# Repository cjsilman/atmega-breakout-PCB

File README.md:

# atmega-breakout-PCB
This PCB project is meant to replicate a simple atmega32u4 microcontroller board with GPIO pinouts. It contains a USB port for programming and powering.

As the idea of designing my own PCB always fascinated me, I thought it would be interesting to give designing one a shot!

While searching around the market for which MCU to use, I choose the ATMEGA32u4 as it comes with a pre-installed bootloader, allowing you to program it via the USB right from the start.
This MCU also came with USB support, something I wanted in my PCB. It was quite the learning process. I feel like I learned quite a bit that I want to share.

To begin with, you typically start by setting up the main components the MCU needs to function: it's power and crystal oscillator.

When designing the schematic for the VCC pins, it is best practice to place a 100nF decoupling capacitor for each pin along with a 10uF bulk decoupling capcitor to help with the stabilization of the input voltage.

For the crystal oscillator, you'll want to calculate the value of the decoupling capacitors associated with it. While it is standard practice to use 22pF capacitors, it is important to choose proper capacitor values to allow for more accurate and stable results from the crystal.

  - The capacitor values can be calculated from a formula like this:
    - C1, C2 = 2*Cload-2*Cstray

  - Cload, or the load capacitance, is retrieved from the datasheet of the specific crystal you choose.
  - Cstray, or the stray capacitance, is typically between a value of 3-5pF.
    - Cstray is the parasitic capacitance formed between two traces separated by a dielectric (in more layman terms, it is caused by a potential difference generated by current carrying traces running in close proximity to one another)

If you ever find yourself lost, the MCU datasheet typically has a lot of guidelines for when it comes to designing with that specific IC. Make sure to follow them.

I placed a GND plane on the entire bottom layer of my PCB. This allows for better signal integrity and more resistance to interference, it also allows you to create a via to ground wherever you need it.
     
  - Using one via per GND pin reduces the issue of potentially creating a ground loop and minimizes noise.

I discovered that USBs are typically designed with something known as "differential pairs"

  - On the schematic below, you can see D+ and D-, the postive and negative sign typically denote differential pairings
  - Differential pair PCB routing is used to create a balanced transmission system able to carry equal and opposite signals.
      - These two lines are usually of equal length
  - Having differential pairs also reduces any unwanted impedence

If you have any advice for me or would like to talk to me about certain design decisions feel free to give me a message! I am always looking to learn new things and improve my knowledge

# Full Schematic

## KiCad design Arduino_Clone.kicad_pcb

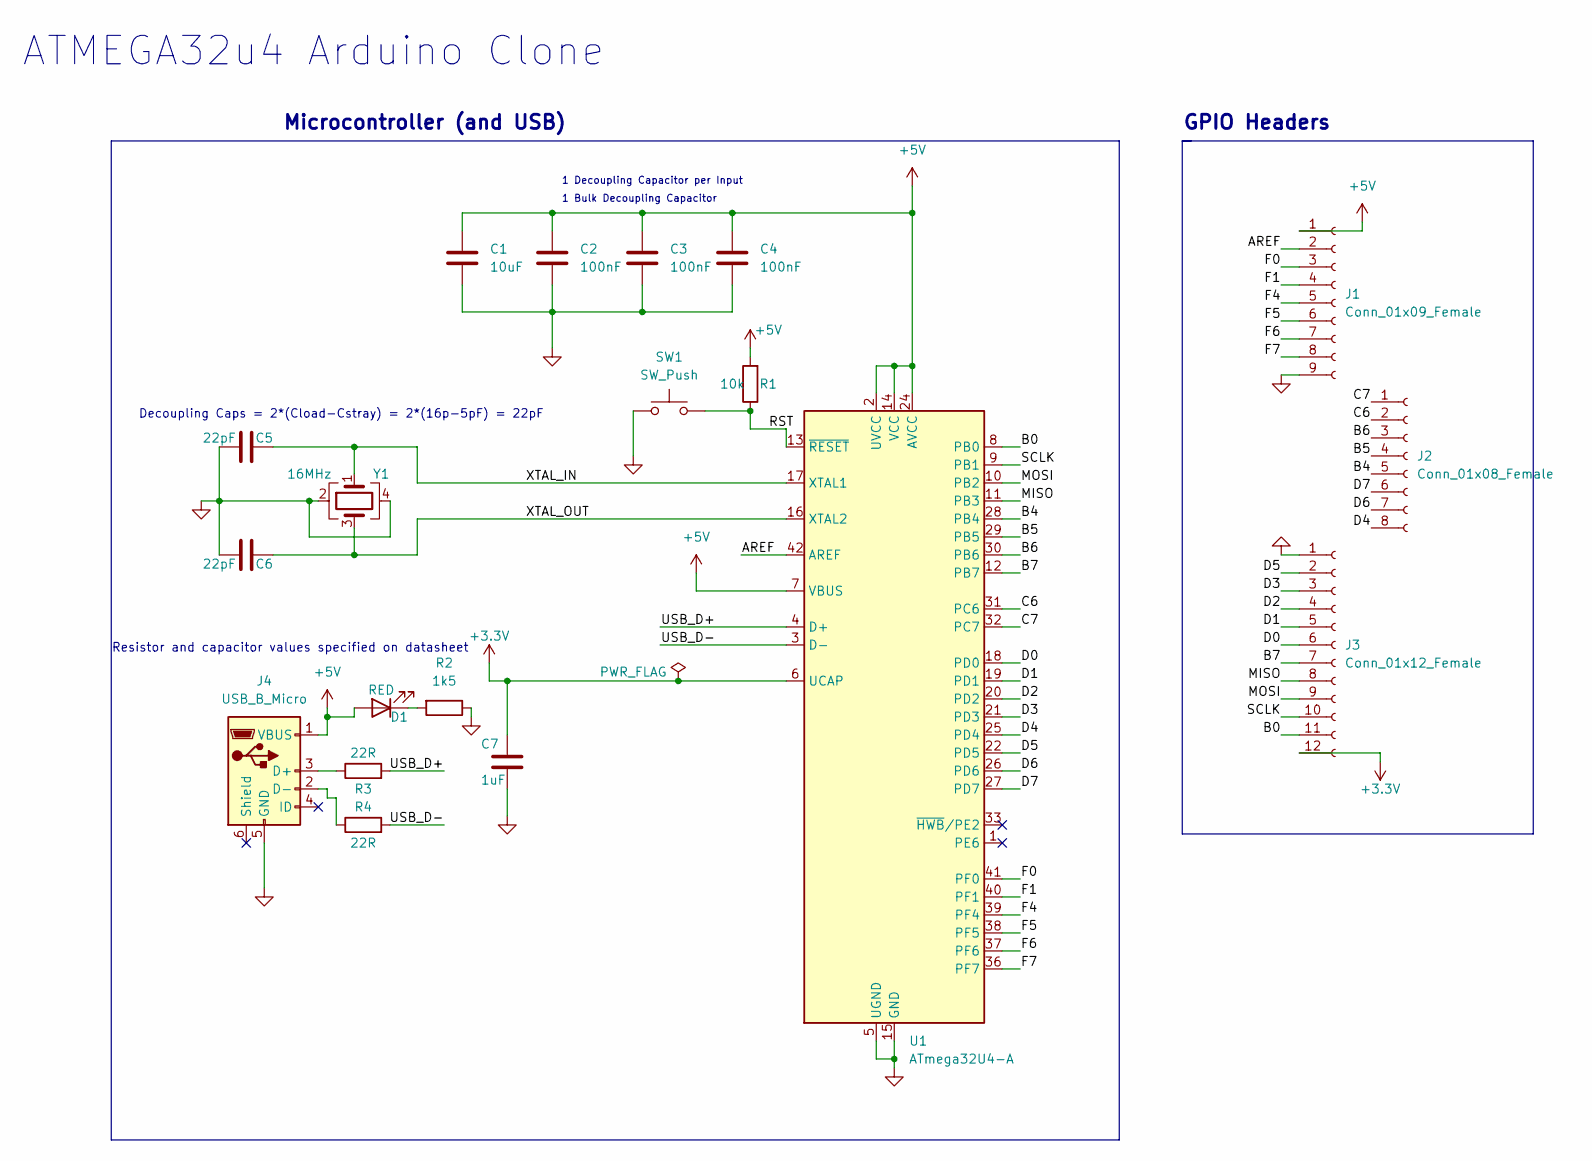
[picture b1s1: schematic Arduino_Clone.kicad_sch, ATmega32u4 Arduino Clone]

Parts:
C1: 10uF; C_0805_2012Metric_Pad1.18x1.45mm_HandSolder
C2, C3, C4: 100nF; C_0805_2012Metric_Pad1.18x1.45mm_HandSolder
C5, C6: 22pF; C_0805_2012Metric_Pad1.18x1.45mm_HandSolder
C7: 1uF; C_0805_2012Metric_Pad1.18x1.45mm_HandSolder
D1: RED; LED_0805_2012Metric_Pad1.15x1.40mm_HandSolder
J1: Conn_01x09_Female; PinSocket_1x09_P2.54mm_Vertical
J2: Conn_01x08_Female; PinSocket_1x08_P2.54mm_Vertical
J3: Conn_01x12_Female; PinSocket_1x12_P2.54mm_Vertical
J4: USB_B_Micro; USB_Micro-B_Wuerth_629105150521
R1: 10k; R_0805_2012Metric_Pad1.20x1.40mm_HandSolder
R2: 1k5; R_0805_2012Metric_Pad1.20x1.40mm_HandSolder
R3, R4: 22R; R_0805_2012Metric_Pad1.20x1.40mm_HandSolder
SW1: SW_Push; SW_Push_1P1T_NO_6x6mm_H9.5mm
U1: ATmega32U4-A; TQFP-44_10x10mm_P0.8mm
Y1: 16MHz; Crystal_SMD_3225-4Pin_3.2x2.5mm

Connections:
+3.3V: C7.1, J3.12, U1.6 (UCAP)
+5V: C1.1, C2.1, C3.1, C4.1, D1.2 (A), J1.1, J4.1 (VBUS), R1.2, U1.2 (UVCC), U1.7 (VBUS), U1.14 (VCC), U1.24 (AVCC), U1.34 (VCC), U1.44 (AVCC)
/AREF: J1.2, U1.42 (AREF)
/B0: J3.11, U1.8 (PB0)
/B4: J2.5, U1.28 (PB4)
/B5: J2.4, U1.29 (PB5)
/B6: J2.3, U1.30 (PB6)
/B7: J3.7, U1.12 (PB7)
/C6: J2.2, U1.31 (PC6)
/C7: J2.1, U1.32 (PC7)
/D0: J3.6, U1.18 (PD0)
/D1: J3.5, U1.19 (PD1)
/D2: J3.4, U1.20 (PD2)
/D3: J3.3, U1.21 (PD3)
/D4: J2.8, U1.25 (PD4)
/D5: J3.2, U1.22 (PD5)
/D6: J2.7, U1.26 (PD6)
/D7: J2.6, U1.27 (PD7)
/F0: J1.3, U1.41 (PF0)
/F1: J1.4, U1.40 (PF1)
/F4: J1.5, U1.39 (PF4)
/F5: J1.6, U1.38 (PF5)
/F6: J1.7, U1.37 (PF6)
/F7: J1.8, U1.36 (PF7)
/MISO: J3.8, U1.11 (PB3)
/MOSI: J3.9, U1.10 (PB2)
/RST: R1.1, SW1.2, U1.13 (~RESET)
/SCLK: J3.10, U1.9 (PB1)
/USB_D+: R3.2, U1.4 (D+)
/USB_D-: R4.2, U1.3 (D-)
/XTAL_IN: C5.2, U1.17 (XTAL1), Y1.1
/XTAL_OUT: C6.2, U1.16 (XTAL2), Y1.3
GND: C1.2, C2.2, C3.2, C4.2, C5.1, C6.1, C7.2, J1.9, J3.1, J4.5 (GND), R2.1, SW1.1, U1.5 (UGND), U1.15 (GND), U1.23 (GND), U1.35 (GND), U1.43 (GND), Y1.2, Y1.4
unnamed: D1.1 (K), R2.2
unnamed: J4.2 (D-), R4.1
unnamed: J4.3 (D+), R3.1

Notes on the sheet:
1 Bulk Decoupling Capacitor
Resistor and capacitor values specified on datasheet
GPIO Headers
ATMEGA32u4 Arduino Clone
1 Decoupling Capacitor per Input
Microcontroller (and USB)
Decoupling Caps = 2*(Cload-Cstray) = 2*(16p-5pF) = 22pF

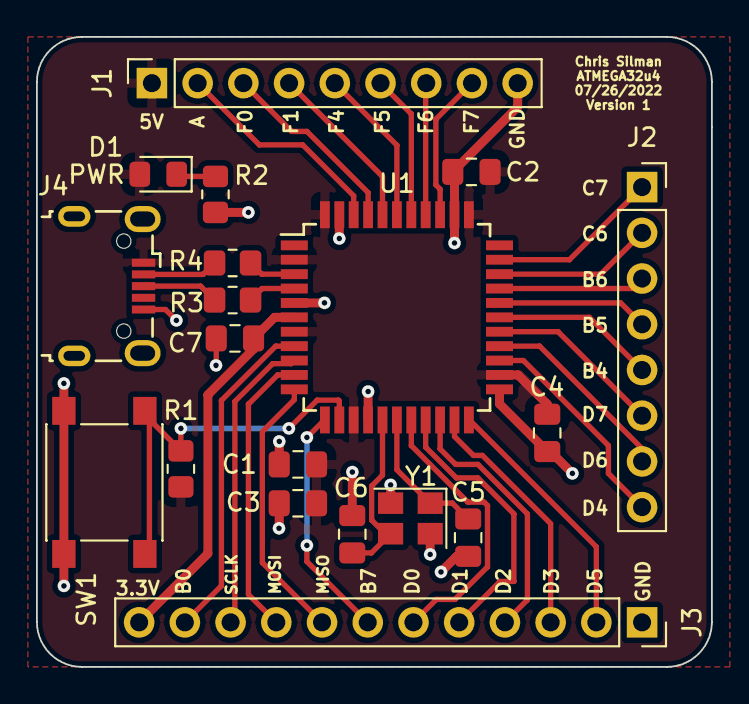
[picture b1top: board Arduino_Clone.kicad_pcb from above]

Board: 2 copper layers, 37.5 x 35.0 mm, 19 parts (0 on the bottom side), 36 nets.

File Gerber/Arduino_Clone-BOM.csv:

"Source:","G:\Desktop\KiCAD projects\Arduino_Clone\Arduino_Clone.kicad_sch"
"Date:","7/26/2022 7:15:45 PM"
"Tool:","Eeschema (6.0.6)"
"Generator:","G:\Program Files\KiCad\6.0\bin\scripting\plugins/bom_csv_grouped_by_value_with_fp.py"
"Component Count:","19"
"Ref","Qnty","Value","Cmp name","Footprint","Description","Vendor"
"C1, ","1","10uF","C","Capacitor_SMD:C_0805_2012Metric_Pad1.18x1.45mm_HandSolder","Unpolarized capacitor",""
"C2, C3, C4, ","3","100nF","C","Capacitor_SMD:C_0805_2012Metric_Pad1.18x1.45mm_HandSolder","Unpolarized capacitor",""
"C5, C6, ","2","22pF","C","Capacitor_SMD:C_0805_2012Metric_Pad1.18x1.45mm_HandSolder","Unpolarized capacitor",""
"C7, ","1","1uF","C","Capacitor_SMD:C_0805_2012Metric_Pad1.18x1.45mm_HandSolder","Unpolarized capacitor",""
"D1, ","1","RED","LED","LED_SMD:LED_0805_2012Metric_Pad1.15x1.40mm_HandSolder","Light emitting diode",""
"J1, ","1","Conn_01x09_Female","Conn_01x09_Female","Connector_PinSocket_2.54mm:PinSocket_1x09_P2.54mm_Vertical","Generic connector, single row, 01x09, script generated (kicad-library-utils/schlib/autogen/connector/)",""
"J2, ","1","Conn_01x08_Female","Conn_01x08_Female","Connector_PinSocket_2.54mm:PinSocket_1x08_P2.54mm_Vertical","Generic connector, single row, 01x08, script generated (kicad-library-utils/schlib/autogen/connector/)",""
"J3, ","1","Conn_01x12_Female","Conn_01x12_Female","Connector_PinSocket_2.54mm:PinSocket_1x12_P2.54mm_Vertical","Generic connector, single row, 01x12, script generated (kicad-library-utils/schlib/autogen/connector/)",""
"J4, ","1","USB_B_Micro","USB_B_Micro","Connector_USB:USB_Micro-B_Wuerth_629105150521","USB Micro Type B connector",""
"R1, ","1","10k","R","Resistor_SMD:R_0805_2012Metric_Pad1.20x1.40mm_HandSolder","Resistor",""
"R2, ","1","1k5","R","Resistor_SMD:R_0805_2012Metric_Pad1.20x1.40mm_HandSolder","Resistor",""
"R3, R4, ","2","22R","R","Resistor_SMD:R_0805_2012Metric_Pad1.20x1.40mm_HandSolder","Resistor",""
"SW1, ","1","SW_Push","SW_Push","Button_Switch_SMD:SW_Push_1P1T_NO_6x6mm_H9.5mm","Push button switch, generic, two pins",""
"U1, ","1","ATmega32U4-A","ATmega32U4-A","Package_QFP:TQFP-44_10x10mm_P0.8mm","16MHz, 32kB Flash, 2.5kB SRAM, 1kB EEPROM, USB 2.0, TQFP-44",""
"Y1, ","1","16MHz","Crystal_GND24","Crystal:Crystal_SMD_3225-4Pin_3.2x2.5mm","Four pin crystal, GND on pins 2 and 4",""

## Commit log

2022-08-01 Create LICENSE
